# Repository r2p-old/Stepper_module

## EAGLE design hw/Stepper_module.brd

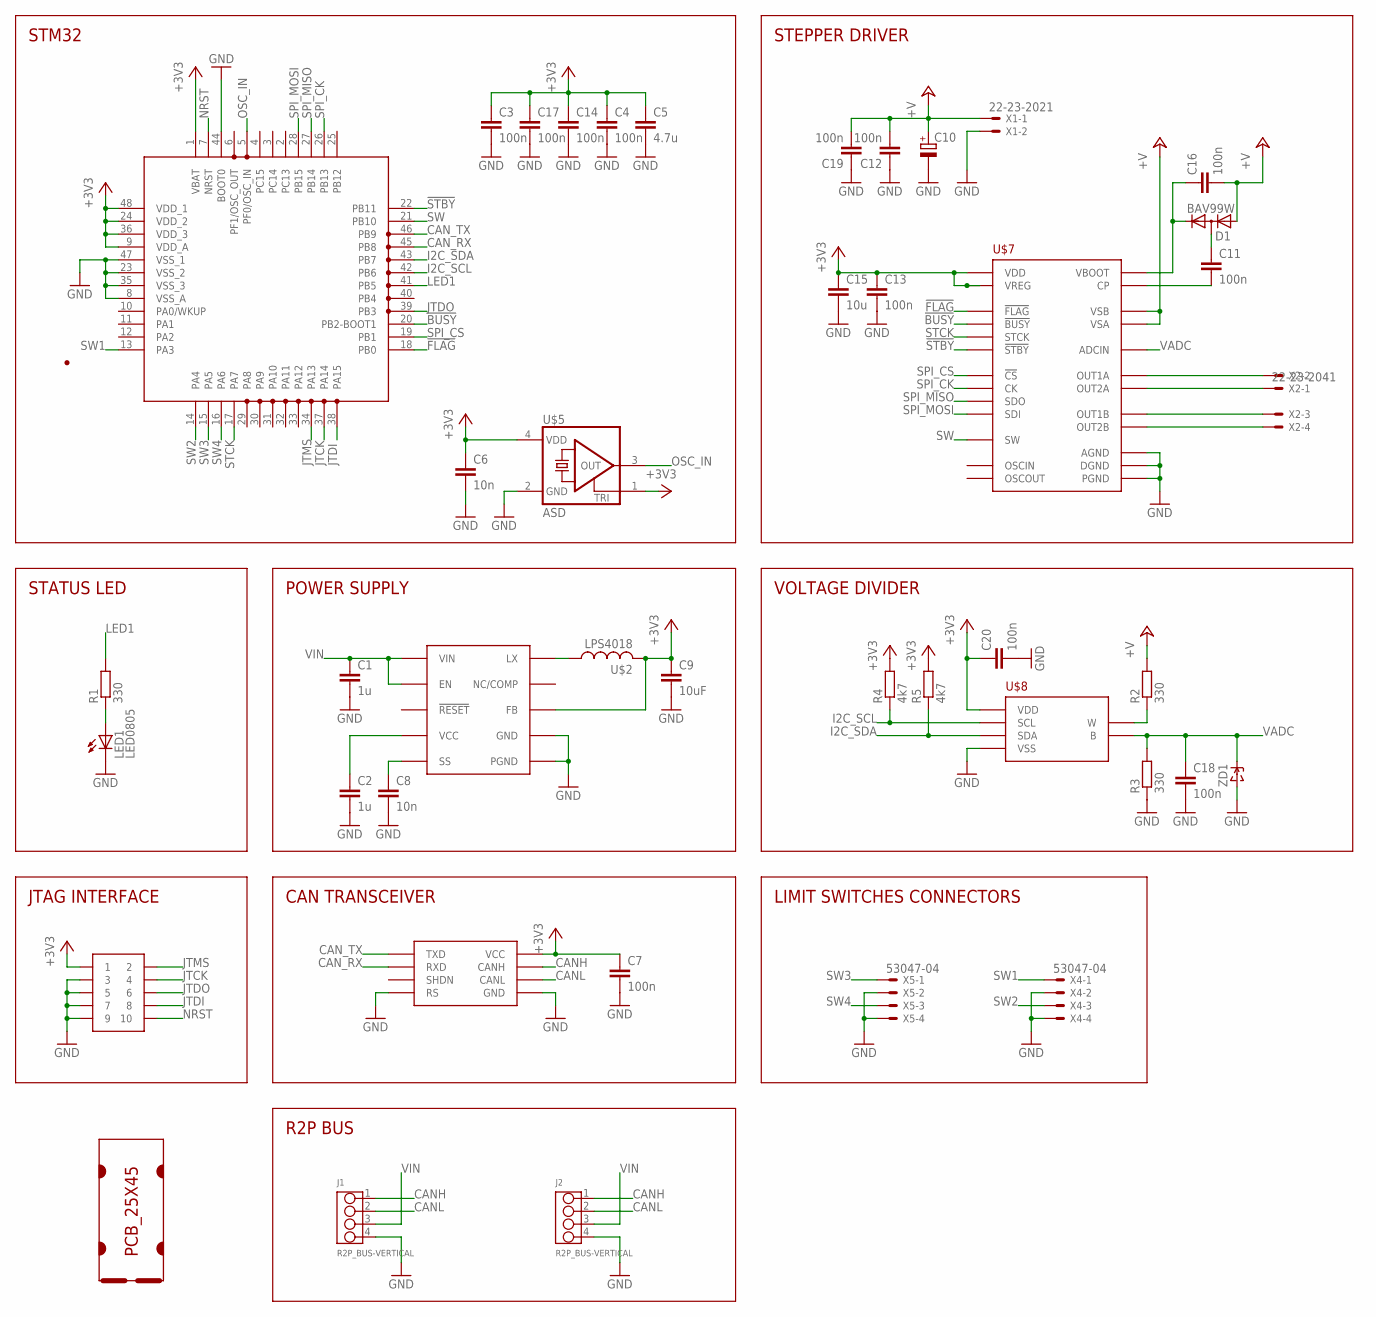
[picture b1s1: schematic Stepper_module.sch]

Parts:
C1: 1u; C1206
C2: 1u; C0603
C3, C4, C7, C11, C12, C13, C14, C16, C17, C18, C19, C20: 100n; C0603
C5: 4.7u; C0805
C6, C8: 10n; C0603
C9: 10uF; C0805
C10: CPOL-EUD; PANASONIC_D
C15: 10u; C0805
D1: BAV99W; SC70
J1, J2: R2P_BUS-VERTICAL; OPL-EAGLE-LIBRARY_4P-2.0
LED1: LED0805; CHIPLED_0805
R1, R2, R3: 330; R0603
R4, R5: 4k7; R0603
SOT1: MAX3051EKA; SOT23-8L
U$1: PCB_25X45; 25X45
U$2: LPS4018
U$3: MAX17501; TDFN-10
U$4: JTAG-TH; SAMTEC_FTSH-105-TH
U$5: ASD; 2.5X2
U$6: STM32F303C; LQFP48
U$7: L6470; HTSSOP28
U$8: MCP4017; SC70-6L
X1: 22-23-2021
X2: 22-23-2041
X4, X5: 53047-04
ZD1: ZENERSOD-323F; SOD-323F

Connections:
!BUSY: U$6.20 (PB2-BOOT1), U$7.P$22 (!BUSY)
!FLAG: U$6.18 (PB0), U$7.P$24 (!FLAG)
!STBY: U$6.22 (PB11), U$7.P$3 (!STBY)
+3V3: C3.1, C4.1, C5.1, C6.1, C7.1, C9.1, C13.1, C14.1, C15.1, C17.1, C20.1, R4.2, R5.2, SOT1.3 (VCC), U$2.P$2 (2), U$3.P$5 (FB), U$4.1, U$5.1 (TRI), U$5.4 (VDD), U$6.1 (VBAT), U$6.9 (VDD_A), U$6.24 (VDD_2), U$6.36 (VDD_3), U$6.48 (VDD_1), U$7.P$6 (VREG), U$7.P$17 (VDD), U$8.1 (VDD)
+V: C10.+, C12.2, C16.2, C19.2, D1.1 (A), R2.2, U$7.P$2 (VSA), U$7.P$12 (VSB), U$7.P$16 (VSB), U$7.P$26 (VSA), X1.1
CANH: J1.1, J2.1, SOT1.7 (CANH)
CANL: J1.2, J2.2, SOT1.6 (CANL)
CAN_RX: SOT1.4 (RXD), U$6.45 (PB8)
CAN_TX: SOT1.1 (TXD), U$6.46 (PB9)
GND: C1.2, C2.2, C3.2, C4.2, C5.2, C6.2, C7.2, C8.2, C9.2, C10.-, C12.1, C13.2, C14.2, C15.2, C17.2, C18.2, C19.1, C20.2, J1.4, J2.4, LED1.C, R3.1, SOT1.2 (GND), SOT1.8 (RS), U$3.P$1 (PGND), U$3.P$9 (GND), U$3.P$11 (PGND), U$4.3, U$4.5, U$4.7, U$4.9, U$5.2 (GND), U$6.8 (VSS_A), U$6.23 (VSS_2), U$6.35 (VSS_3), U$6.44 (BOOT0), U$6.47 (VSS_1), U$7.P$9 (AGND), U$7.P$13 (PGND), U$7.P$21 (DGND), U$7.P$27 (PGND), U$7.P$29 (PGND), U$8.2 (VSS), X1.2, X4.2, X4.4, X5.2, X5.4, ZD1.A
I2C_SCL: R4.1, U$6.42 (PB6), U$8.3 (SCL)
I2C_SDA: R5.1, U$6.43 (PB7), U$8.4 (SDA)
JTCK: U$4.4, U$6.37 (PA14)
JTDI: U$4.8, U$6.38 (PA15)
JTDO: U$4.6, U$6.39 (PB3)
JTMS: U$4.2, U$6.34 (PA13)
LED1: R1.2, U$6.41 (PB5)
unnamed: U$2.P$1 (1), U$3.P$10 (LX)
unnamed: U$7.P$28 (OUT2A), X2.1
unnamed: LED1.A, R1.1
unnamed: U$7.P$1 (OUT1A), X2.2
unnamed: U$7.P$14 (OUT1B), X2.3
unnamed: C2.1, U$3.P$4 (VCC)
unnamed: C8.1, U$3.P$6 (SS)
unnamed: U$7.P$15 (OUT2B), X2.4
unnamed: R2.1, U$8.6 (W)
unnamed: C11.1, D1.3 (AC)
unnamed: C11.2, U$7.P$10 (CP)
unnamed: C16.1, D1.2 (C), U$7.P$11 (VBOOT)
NRST: U$4.10, U$6.7 (NRST)
OSC_IN: U$5.3 (OUT), U$6.5 (PF0/OSC_IN)
SPI_CK: U$6.26 (PB13), U$7.P$19 (CK)
SPI_CS: U$6.19 (PB1), U$7.P$23 (!CS)
SPI_MISO: U$6.27 (PB14), U$7.P$18 (SDO)
SPI_MOSI: U$6.28 (PB15), U$7.P$20 (SDI)
STCK: U$6.17 (PA7), U$7.P$25 (STCK)
SW: U$6.21 (PB10), U$7.P$4 (SW)
SW1: U$6.13 (PA3), X4.1
SW2: U$6.14 (PA4), X4.3
SW3: U$6.15 (PA5), X5.1
SW4: U$6.16 (PA6), X5.3
VADC: C18.1, R3.2, U$7.P$5 (ADCIN), U$8.5 (B), ZD1.C
VIN: C1.1, J1.3, J2.3, U$3.P$2 (VIN), U$3.P$3 (EN)

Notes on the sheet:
STM32
STATUS LED
JTAG INTERFACE
POWER SUPPLY
CAN TRANSCEIVER
R2P BUS
STEPPER DRIVER
VOLTAGE DIVIDER
LIMIT SWITCHES CONNECTORS

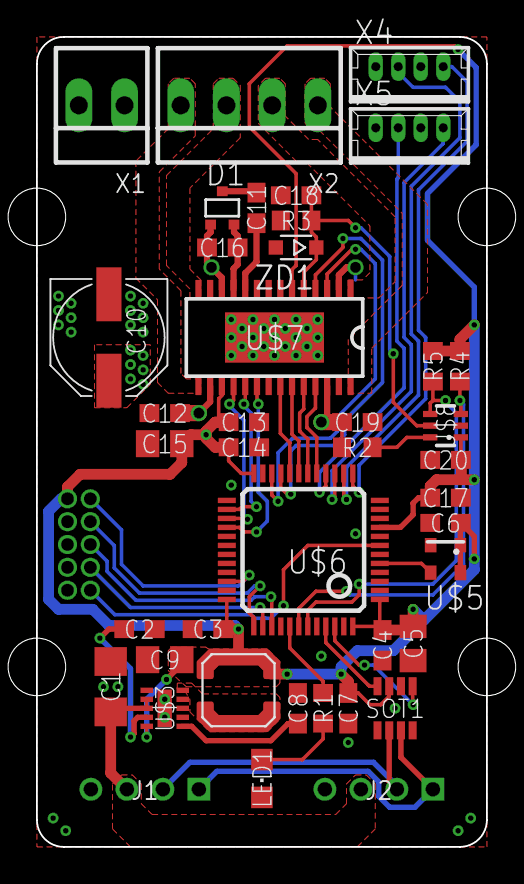
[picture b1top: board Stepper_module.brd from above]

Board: 2 copper layers, 25.0 x 45.0 mm, 43 parts (0 on the bottom side), 43 nets.

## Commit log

2015-01-28 Layout completed
2015-01-31 Minor updates
2015-02-19 Fixed directory creation
2015-02-19 Added bottom silkscreen
2015-02-19 Updated components to R2P Eagle libraries
